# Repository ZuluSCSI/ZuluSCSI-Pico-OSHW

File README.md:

ZuluSCSI™ Pico Community Edition - Open Source Hardware
========================

This repository contains the KiCAD 7 schematic and PCB design files for the Pico-based ZuluSCSI™ SCSI to SD storage emulator, which is derived from the ZuluSCSI RP2040 board design. Firmware for ZuluSCSI is available at http://github.com/ZuluSCSI/ZuluSCSI-firmware.

This hardware design is licensed under the terms of the strongly reciprocal CERN OHL-S V2 license, which can be viewed in full at https://ohwr.org/cern_ohl_s_v2.txt and https://ohwr.org/cern_ohl_s_v2.pdf. 

ZuluSCSI™ is a registered trademark of Rabbit Hole Computing, and may not be used commercially without the express written consent of Rabbit Hole Computing. Individuals producing ZuluSCSI boards for personal use are hereby granted permission to use the ZuluSCSI trademark in a noncommercial capacity.

_Any_ use of the ZuluSCSI trademark in a **commercial** context requires prior written consent from Rabbit Hole Computing.

Generating fabrication files
----------------------------

The component part numbers are stored in KiCAD schematic.
Manufacturing files, including assembly BOM, can be generated using [KiKit](https://github.com/yaqwsx/KiKit).

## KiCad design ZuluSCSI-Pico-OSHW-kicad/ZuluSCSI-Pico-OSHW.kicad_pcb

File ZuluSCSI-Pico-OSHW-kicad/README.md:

ZuluSCSI™ Pico Community Edition - Open Source Hardware
========================

This repository contains the KiCAD 7 schematic and PCB design files for the Pico-based ZuluSCSI™ SCSI to SD storage emulator, which is derived from the ZuluSCSI RP2040 board design. Firmware for ZuluSCSI is available at http://github.com/ZuluSCSI/ZuluSCSI-firmware.

This hardware design is licensed under the terms of the strongly reciprocal CERN OHL-S V2 license, which can be viewed in full at https://ohwr.org/cern_ohl_s_v2.txt and https://ohwr.org/cern_ohl_s_v2.pdf. 

ZuluSCSI™ is a registered trademark of Rabbit Hole Computing, and may not be used commercially without the express written consent of Rabbit Hole Computing. Individuals producing ZuluSCSI boards for personal use are hereby granted permission to use the ZuluSCSI trademark in a noncommercial capacity.

_Any_ use of the ZuluSCSI trademark in a **commercial** context requires prior written consent from Rabbit Hole Computing.

Firmware for ZuluSCSI is licensed under the GNU GPL Version 3, and can be found at https://github.com/zuluscsi/ZuluSCSI-firmware

Generating fabrication files
----------------------------

The component part numbers are stored in KiCAD schematic.
Manufacturing files, including assembly BOM, can be generated using [KiKit](https://github.com/yaqwsx/KiKit).

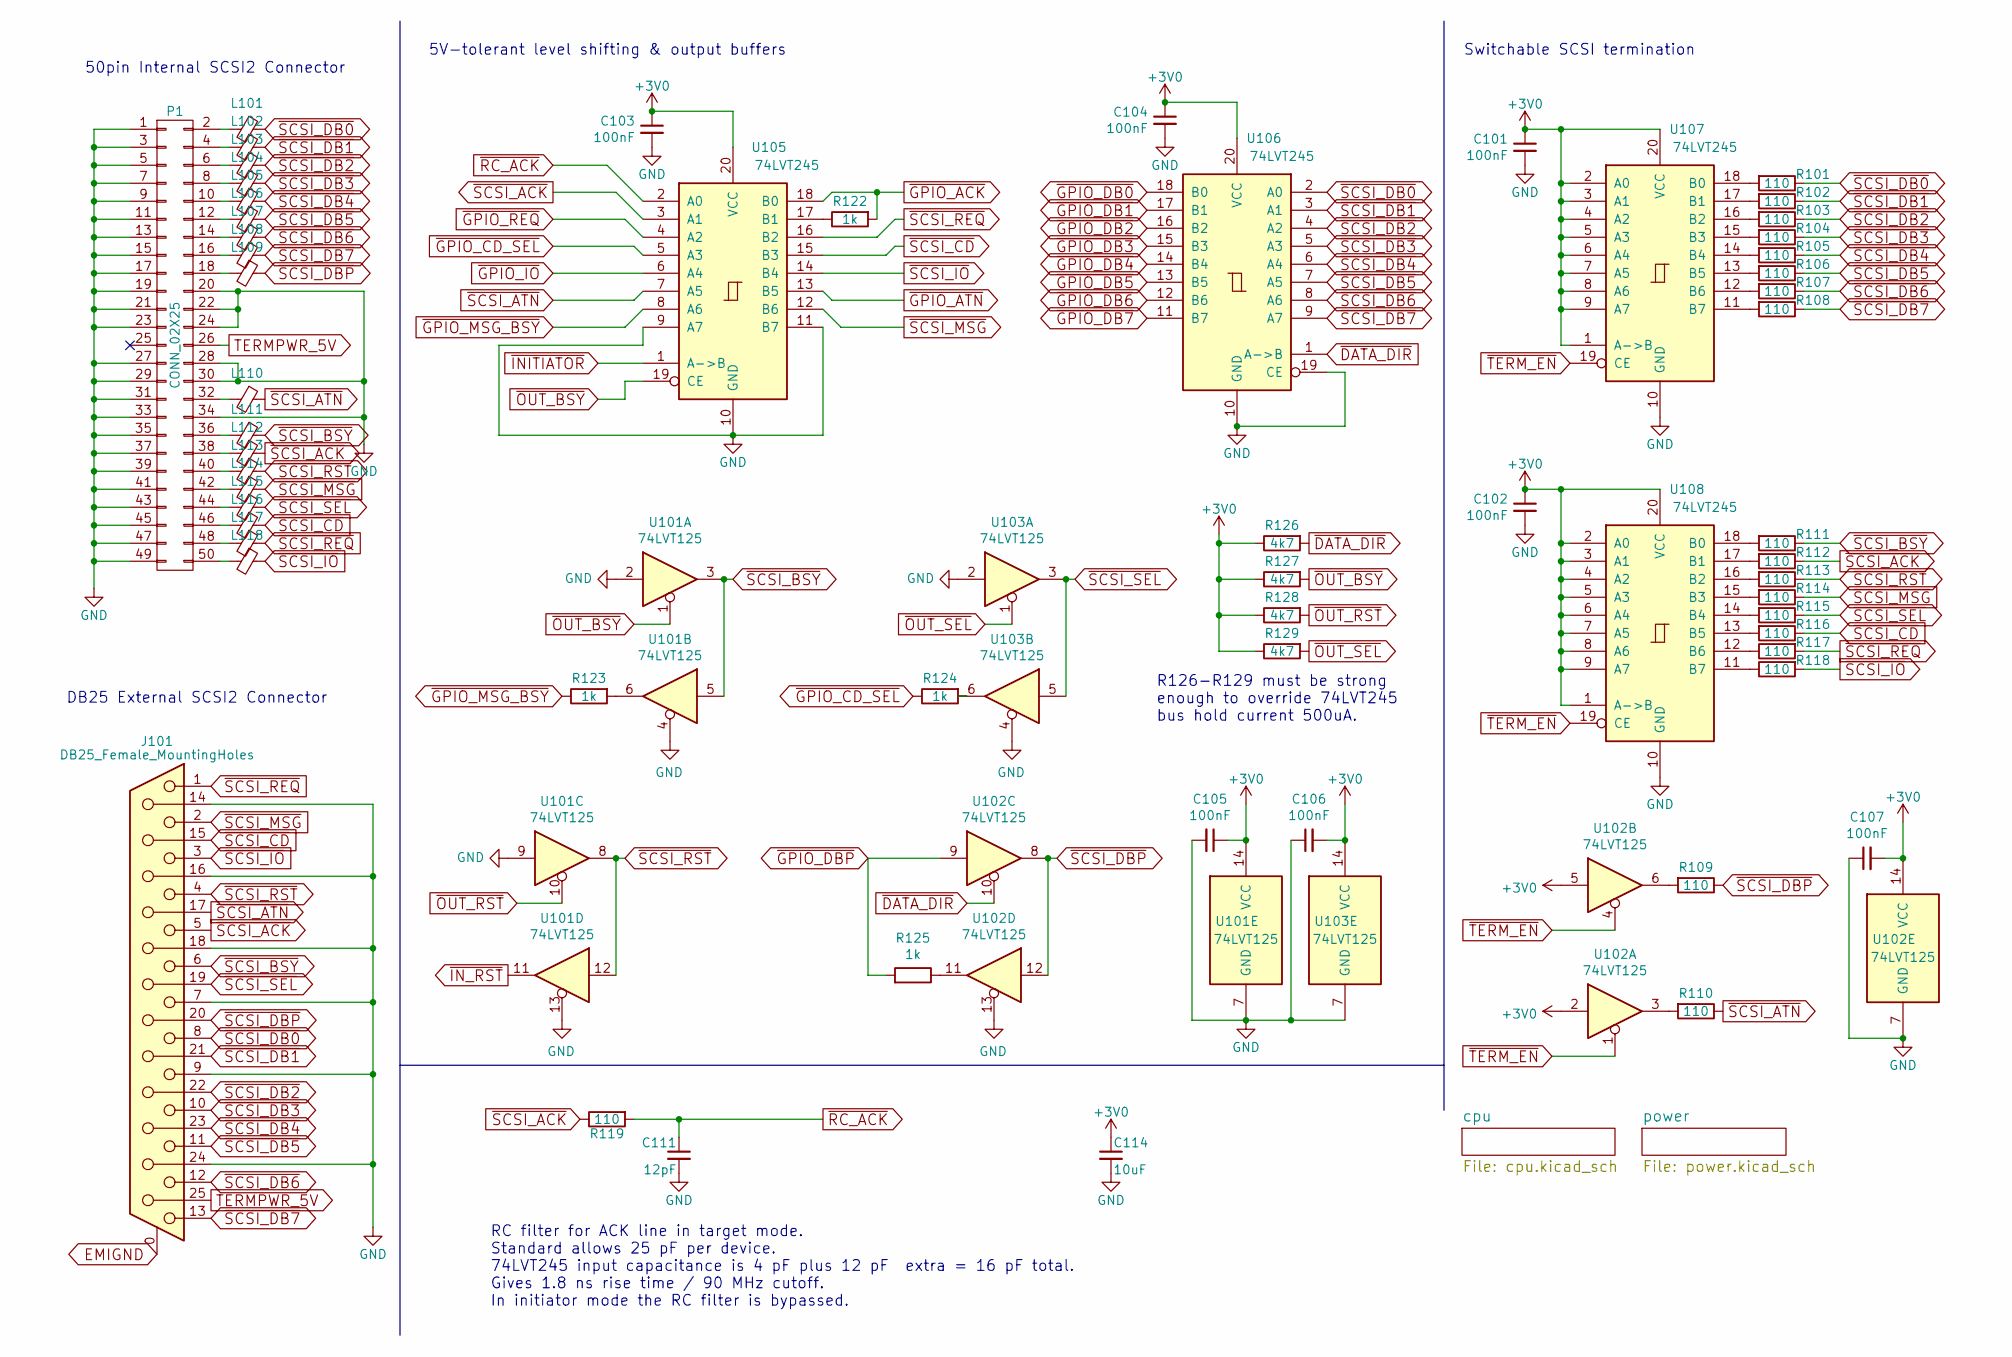
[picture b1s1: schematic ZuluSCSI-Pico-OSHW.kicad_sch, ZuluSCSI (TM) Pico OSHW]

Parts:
C101, C102, C103, C104, C105, C106, C107: 100nF; C_0603_1608Metric; PartNumber CL10B104KB8NNWC; LCSC C14663
C111: 12pF; C_0603_1608Metric; PartNumber C0603C120J5GAC7867; LCSC C38523
C114: 10uF; C_0805_2012Metric; PartNumber CL21A106KPFNNNG; LCSC C15850
J101: DB25_Female_MountingHoles; DSUB-25_Female_Horizontal_P2.77x2.84mm_EdgePinOffset9.90mm_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; LCSC N/A
L101, L102, L103, L104, L105, L106, L107, L108, L109, L110, L111, L112, L113, L114, L115, L116, L117, L118: Ferrite_Bead_Small; L_0603_1608Metric; PartNumber PE-0603FB601ST; LCSC C1002
P1: CONN_02X25; Pin_Header_Angled_2x25; LCSC N/A
R101, R102, R103, R104, R105, R106, R107, R108, R109, R110, R111, R112, R113, R114, R115, R116, R117, R118, R119: 110; R_0603_1608Metric; PartNumber RC0603FR-07110RL; LCSC C22781
R122, R123, R124, R125: 1k; R_0603_1608Metric; PartNumber RC0603JR-071KL; LCSC C21190
R126, R127, R128, R129: 4k7; R_0603_1608Metric; PartNumber RC0603JR-074K7L; LCSC C23162
U101, U102, U103: 74LVT125; SSOP_TSSOP-14_4.4x5mm_Pitch0.65mm_PCBWay-MaskClearance0.22mm; PartNumber 74LVTH125MTC; LCSC C7042
U105, U106, U107, U108: 74LVT245; SSOP_TSSOP-20_5.3x7.2mm_P0.65mm; PartNumber 74LVT245BBT20-13; LCSC C7057

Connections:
+3V0: C101.1, C102.1, C103.1, C104.1, C105.1, C106.2, C107.2, C114.1, R126.1, R127.1, R128.1, R129.1, U101.14 (VCC), U102.2, U102.5, U102.14 (VCC), U103.14 (VCC), U105.20 (VCC), U106.20 (VCC), U107.1 (A->B), U107.2 (A0), U107.3 (A1), U107.4 (A2), U107.5 (A3), U107.6 (A4), U107.7 (A5), U107.8 (A6), U107.9 (A7), U107.20 (VCC), U108.1 (A->B), U108.2 (A0), U108.3 (A1), U108.4 (A2), U108.5 (A3), U108.6 (A4), U108.7 (A5), U108.8 (A6), U108.9 (A7), U108.20 (VCC); also elsewhere on the board
EMIGND: J101.0 (PAD); also elsewhere on the board
GND: C101.2, C102.2, C103.2, C104.2, C105.2, C106.1, C107.1, C111.2, C114.2, J101.7, J101.9, J101.14, J101.16, J101.18, J101.24, P1.1, P1.3, P1.5, P1.7, P1.9, P1.11, P1.13, P1.15, P1.17, P1.19, P1.20, P1.21, P1.22, P1.23, P1.24, P1.27, P1.28, P1.29, P1.30, P1.31, P1.33, P1.34, P1.35, P1.37, P1.39, P1.41, P1.43, P1.45, P1.47, P1.49, U101.2, U101.4, U101.7 (GND), U101.9, U101.13, U102.7 (GND), U102.13, U103.2, U103.4, U103.7 (GND), U105.9 (A7), U105.10 (GND), U105.11 (B7), U106.10 (GND), U106.19 (CE), U107.10 (GND), U108.10 (GND); also elsewhere on the board
unnamed: L101.2, P1.2
unnamed: L102.2, P1.4
unnamed: L103.2, P1.6
unnamed: L104.2, P1.8
unnamed: L105.2, P1.10
unnamed: L106.2, P1.12
unnamed: L107.2, P1.14
unnamed: L108.2, P1.16
unnamed: L109.2, P1.18
unnamed: L110.2, P1.32
unnamed: L111.2, P1.36
unnamed: L112.2, P1.38
unnamed: L113.2, P1.40
unnamed: L114.2, P1.42
unnamed: L115.2, P1.44
unnamed: L116.2, P1.46
unnamed: L117.2, P1.48
unnamed: L118.2, P1.50
unnamed: R109.2, U102.6
unnamed: R110.2, U102.3
unnamed: R123.2, U101.6
unnamed: R124.2, U103.6
unnamed: R125.1, U102.11
unnamed: R122.1, U105.17 (B1)
unnamed: R101.2, U107.18 (B0)
unnamed: R102.2, U107.17 (B1)
unnamed: R103.2, U107.16 (B2)
unnamed: R104.2, U107.15 (B3)
unnamed: R105.2, U107.14 (B4)
unnamed: R106.2, U107.13 (B5)
unnamed: R107.2, U107.12 (B6)
unnamed: R108.2, U107.11 (B7)
unnamed: R111.2, U108.18 (B0)
unnamed: R112.2, U108.17 (B1)
unnamed: R113.2, U108.16 (B2)
unnamed: R114.2, U108.15 (B3)
unnamed: R115.2, U108.14 (B4)
unnamed: R116.2, U108.13 (B5)
unnamed: R117.1, U108.12 (B6)
unnamed: R118.1, U108.11 (B7)
TERMPWR_5V: J101.25, P1.26; also elsewhere on the board
~DATA_DIR: R126.2, U102.10, U106.1 (A->B); also elsewhere on the board
~GPIO_ACK: R122.2, U105.18 (B0); also elsewhere on the board
~GPIO_ATN: U105.13 (B5); also elsewhere on the board
~GPIO_CD_SEL: R124.1, U105.5 (A3); also elsewhere on the board
~GPIO_DB0: U106.18 (B0); also elsewhere on the board
~GPIO_DB1: U106.17 (B1); also elsewhere on the board
~GPIO_DB2: U106.16 (B2); also elsewhere on the board
~GPIO_DB3: U106.15 (B3); also elsewhere on the board
~GPIO_DB4: U106.14 (B4); also elsewhere on the board
~GPIO_DB5: U106.13 (B5); also elsewhere on the board
~GPIO_DB6: U106.12 (B6); also elsewhere on the board
~GPIO_DB7: U106.11 (B7); also elsewhere on the board
~GPIO_DBP: R125.2, U102.9; also elsewhere on the board
~GPIO_IO: U105.6 (A4); also elsewhere on the board
~GPIO_MSG_BSY: R123.1, U105.8 (A6); also elsewhere on the board
~GPIO_REQ: U105.4 (A2); also elsewhere on the board
~INITIATOR: U105.1 (A->B); also elsewhere on the board
~IN_RST: U101.11; also elsewhere on the board
~OUT_BSY: R127.2, U101.1, U105.19 (CE); also elsewhere on the board
~OUT_RST: R128.2, U101.10; also elsewhere on the board
~OUT_SEL: R129.2, U103.1; also elsewhere on the board
~RC_ACK: C111.1, R119.2, U105.2 (A0)
~SCSI_ACK: J101.5, L112.1, R112.1, R119.1, U105.3 (A1)
~SCSI_ATN: J101.17, L110.1, R110.1, U105.7 (A5)
~SCSI_BSY: J101.6, L111.1, R111.1, U101.3, U101.5
~SCSI_CD: J101.15, L116.1, R116.1, U105.15 (B3)
~SCSI_DB0: J101.8, L101.1, R101.1, U106.2 (A0)
~SCSI_DB1: J101.21, L102.1, R102.1, U106.3 (A1)
~SCSI_DB2: J101.22, L103.1, R103.1, U106.4 (A2)
~SCSI_DB3: J101.10, L104.1, R104.1, U106.5 (A3)
~SCSI_DB4: J101.23, L105.1, R105.1, U106.6 (A4)
~SCSI_DB5: J101.11, L106.1, R106.1, U106.7 (A5)
~SCSI_DB6: J101.12, L107.1, R107.1, U106.8 (A6)
~SCSI_DB7: J101.13, L108.1, R108.1, U106.9 (A7)
~SCSI_DBP: J101.20, L109.1, R109.1, U102.8, U102.12
~SCSI_IO: J101.3, L118.1, R118.2, U105.14 (B4)
~SCSI_MSG: J101.2, L114.1, R114.1, U105.12 (B6)
~SCSI_REQ: J101.1, L117.1, R117.2, U105.16 (B2)
~SCSI_RST: J101.4, L113.1, R113.1, U101.8, U101.12
~SCSI_SEL: J101.19, L115.1, R115.1, U103.3, U103.5
~TERM_EN: U102.1, U102.4, U107.19 (CE), U108.19 (CE); also elsewhere on the board

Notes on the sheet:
Switchable SCSI termination
R126-R129 must be strong enough to override 74LVT245 bus hold current 500uA.
5V-tolerant level shifting & output buffers
50pin Internal SCSI2 Connector
DB25 External SCSI2 Connector
RC filter for ACK line in target mode. Standard allows 25 pF per device. 74LVT245 input capacitance is 4 pF plus 12 pF extra = 16 pF total. Gives 1.8 ns rise time / 90 MHz cutoff. In initiator mode the RC filter is bypassed.

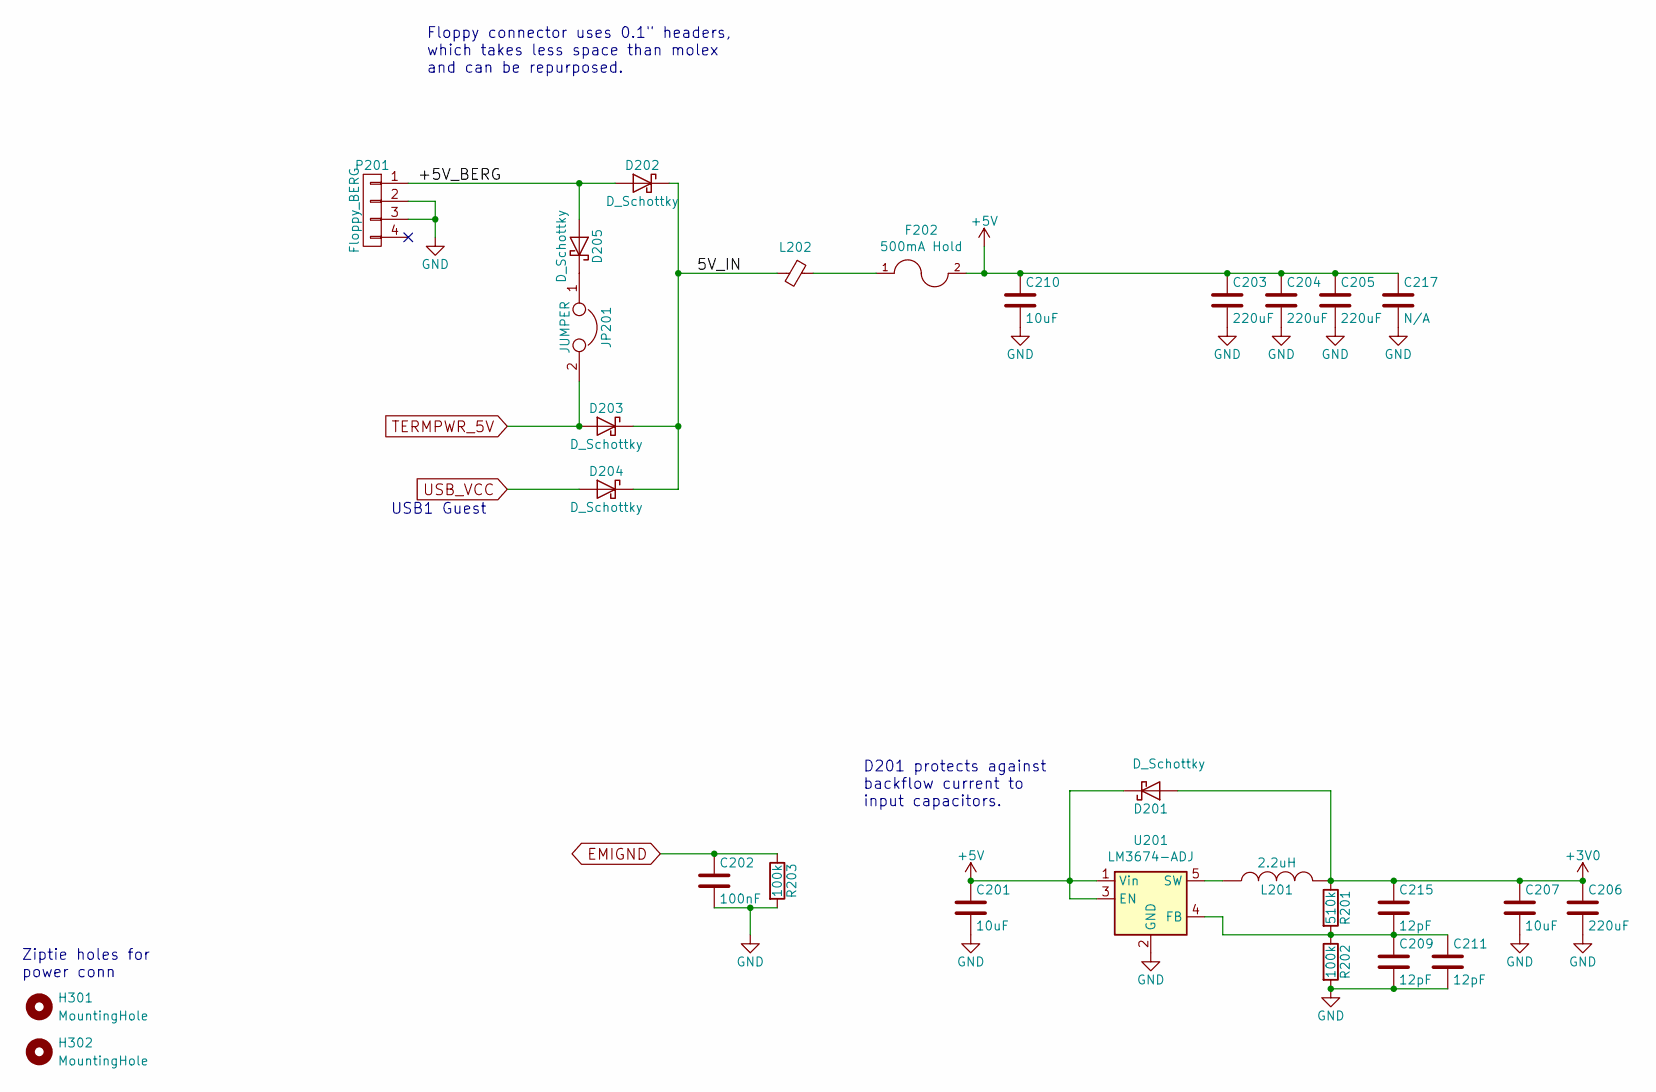
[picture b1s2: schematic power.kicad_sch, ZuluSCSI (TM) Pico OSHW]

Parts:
C201, C207, C210: 10uF; C_0805_2012Metric; PartNumber CL21A106KPFNNNG; LCSC C15850
C202: 100nF; C_0603_1608Metric; PartNumber CL10B104KB8NNWC; LCSC C14663
C203, C204, C205, C206: 220uF; CP_Elec_6.3x7.7; PartNumber UUD1C221MCL1GS; LCSC C2887273
C209, C211, C215: 12pF; C_0603_1608Metric; PartNumber C0603C120J5GAC7867; LCSC C38523
C217: N/A; CP_Radial_D10.0mm_P5.00mm; LCSC N/A
D201, D202, D203, D204, D205: D_Schottky; D_SOD-123; PartNumber MBRX120LF-TP; LCSC C8598
F202: 500mA Hold; Fuse_1206_3216Metric; PartNumber 0ZCJ0050FF2G; LCSC C369160
H301, H302: MountingHole; MountingHole_2.7mm_M2.5; LCSC N/A
JP201: JUMPER; PinHeader_1x02_P2.54mm_Vertical; LCSC N/A
L201: 2.2uH; Inductor_1008; PartNumber DFE252012P-2R2M=P2; LCSC C86092
L202: Ferrite_Bead_Small; L_0603_1608Metric; PartNumber PE-0603FB601ST; LCSC C1002
P201: Floppy_BERG; floppy-berg; LCSC N/A
R201: 510k; R_0603_1608Metric; PartNumber RC0603FR-07510KL; LCSC C23192
R202, R203: 100k; R_0603_1608Metric; PartNumber RC0603FR-07100KL; LCSC C25803
U201: LM3674-ADJ; TSOT-23-5; PartNumber LM3674MFX-ADJ/NOPB; LCSC C52027

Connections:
+3V0: C206.1, C207.1, C215.1, D201.2 (A), L201.2, R201.1; also elsewhere on the board
+5V: C201.1, C203.1, C204.1, C205.1, C210.1, C217.1, D201.1 (K), F202.2, U201.1 (Vin), U201.3 (EN); also elsewhere on the board
/power/5V_IN: D202.1 (K), D203.1 (K), D204.1 (K), L202.2
/power/+5V_BERG: D202.2 (A), D205.2 (A), P201.1
EMIGND: C202.1, R203.1; also elsewhere on the board
GND: C201.2, C202.2, C203.2, C204.2, C205.2, C206.2, C207.2, C209.2, C210.2, C211.2, C217.2, P201.2, P201.3, R202.2, R203.2, U201.2 (GND); also elsewhere on the board
unnamed: D205.1 (K), JP201.1
unnamed: F202.1, L202.1
unnamed: C209.1, C211.1, C215.2, R201.2, R202.1, U201.4 (FB)
unnamed: L201.1, U201.5 (SW)
TERMPWR_5V: D203.2 (A), JP201.2; also elsewhere on the board
USB_VCC: D204.2 (A); also elsewhere on the board

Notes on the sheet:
Floppy connector uses 0.1" headers, which takes less space than molex and can be repurposed.
USB1 Guest
D201 protects against backflow current to input capacitors.
Ziptie holes for power conn

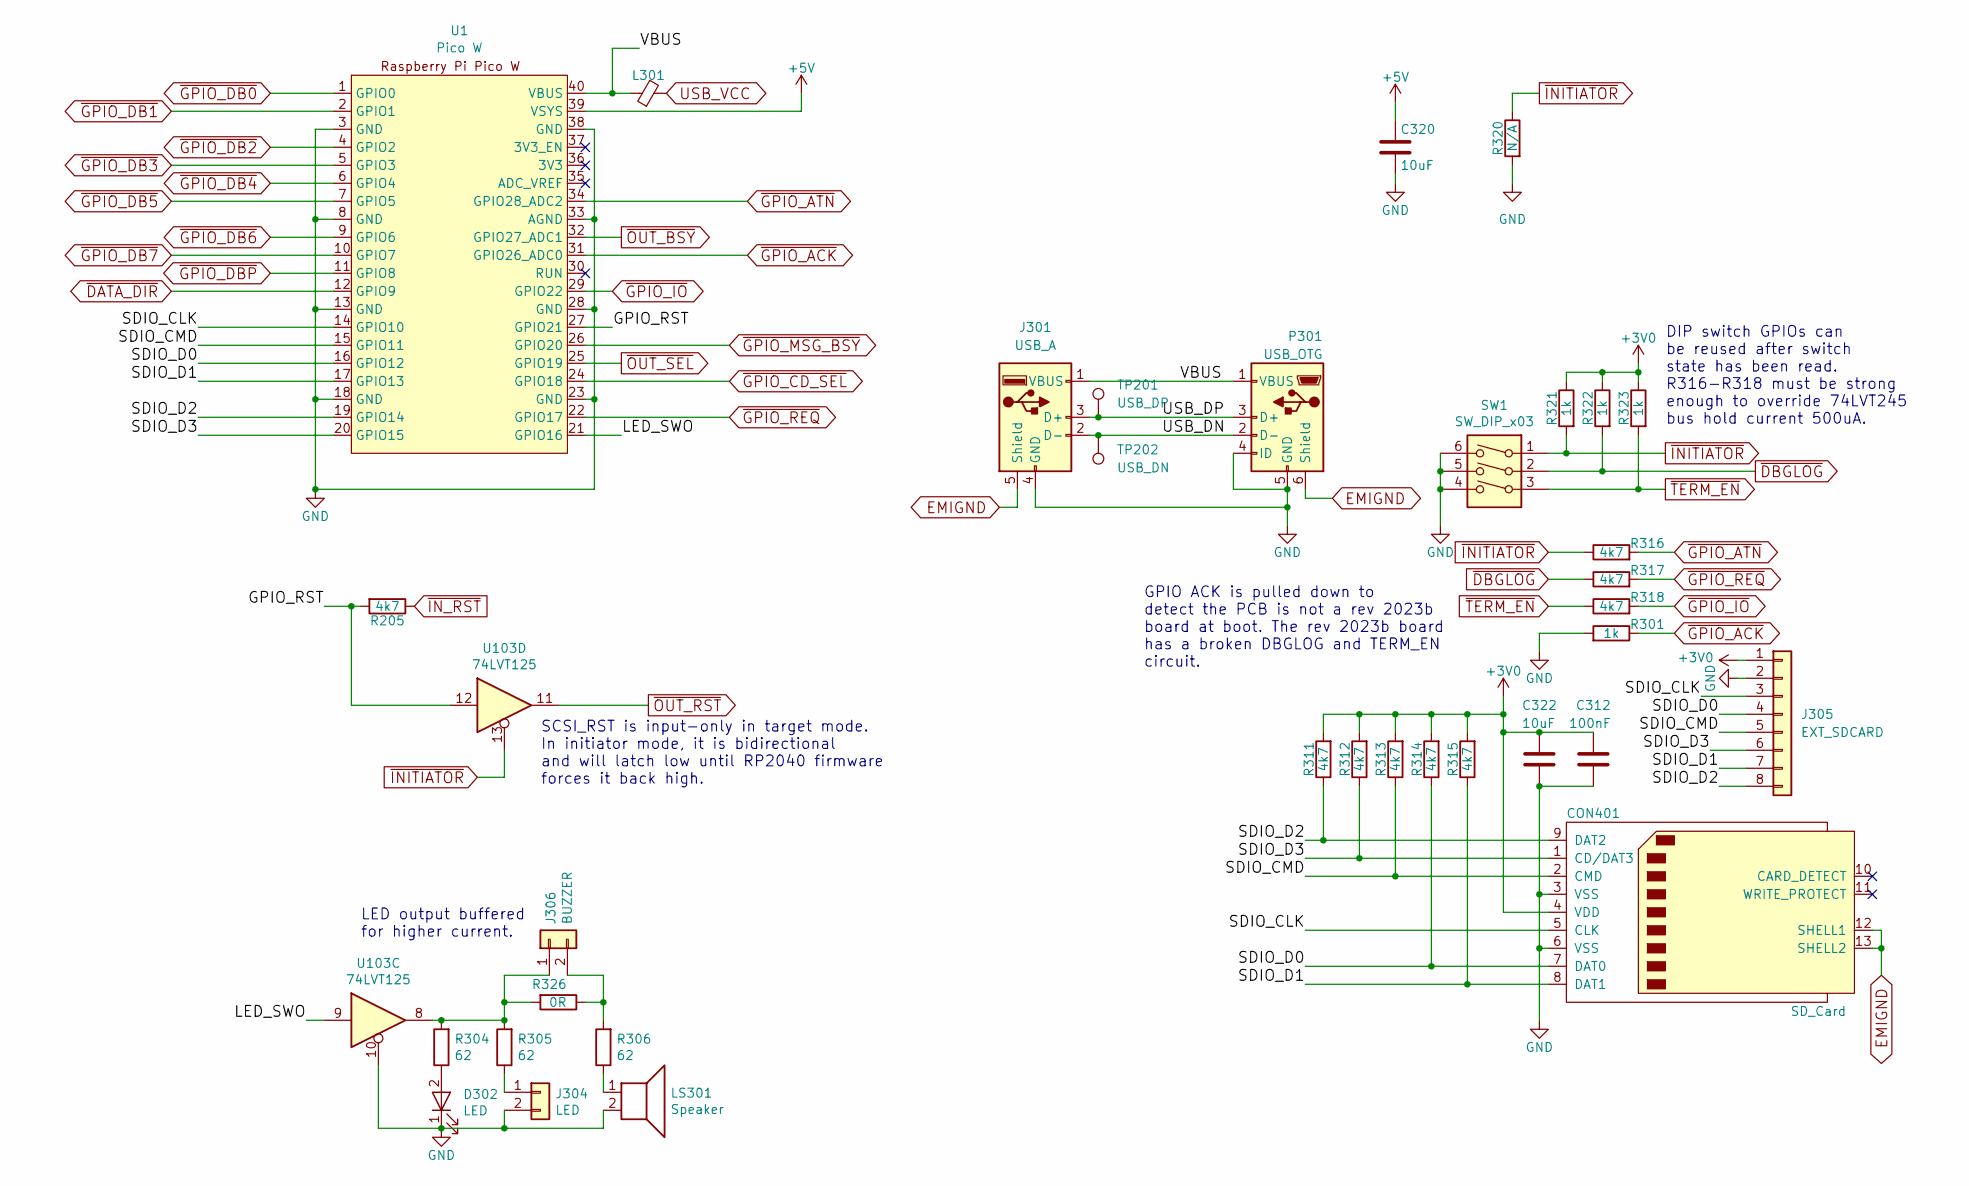
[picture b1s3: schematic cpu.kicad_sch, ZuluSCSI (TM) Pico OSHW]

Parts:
C312: 100nF; C_0603_1608Metric; PartNumber CL10B104KB8NNWC; LCSC C14663
C320, C322: 10uF; C_0805_2012Metric; PartNumber CL21A106KPFNNNG; LCSC C15850
CON401: SD_Card; SD-FCI-10067847-001; PartNumber 10067847-001RLF; LCSC C410353
D302: LED; LED_0805_2012Metric; PartNumber LY R976-PS-36; LCSC C434435
J301: USB_A; USB_A_Molex_105057_Vertical; LCSC N/A
J304: LED; PinHeader_1x02_P2.54mm_Vertical; LCSC N/A
J305: EXT_SDCARD; PinHeader_1x08_P2.54mm_Vertical; JLCPCB_IGNORE do not fit
J306: BUZZER; PinHeader_1x02_P2.54mm_Vertical; LCSC N/A
L301: Ferrite_Bead_Small; L_0603_1608Metric; PartNumber PE-0603FB601ST; LCSC C1002
LS301: Speaker; Buzzer_TDK_PS1240P02BT_D12.2mm_H6.5mm; LCSC N/A
P301: USB_OTG; USB_Micro-B_Amphenol_10118194_Horizontal; PartNumber 10118194-0001LF; LCSC C132563
R205, R311, R312, R313, R314, R315, R316, R317, R318: 4k7; R_0603_1608Metric; PartNumber RC0603JR-074K7L; LCSC C23162
R301, R321, R322, R323: 1k; R_0603_1608Metric; PartNumber RC0603JR-071KL; LCSC C21190
R304, R305, R306: 62; R_0603_1608Metric; PartNumber RC0603FR-0762RL; LCSC C25252
R320: N/A; R_0402_1005Metric; LCSC N/A
R326: 0R; R_0603_1608Metric; LCSC N/A
SW1: SW_DIP_x03; SW_DIP_SPSTx03_Slide_6.7x9.18mm_W8.61mm_P2.54mm_LowProfile; PartNumber 219-3MSTR; LCSC C319040
TP201: USB_DP; TestPoint_Pad_2.0x2.0mm; LCSC N/A
TP202: USB_DN; TestPoint_Pad_2.0x2.0mm; LCSC N/A
U1: Pico W; RPi_Pico_W_SMD_TH; LCSC N/A
U103: 74LVT125; SSOP_TSSOP-14_4.4x5mm_Pitch0.65mm_PCBWay-MaskClearance0.22mm; PartNumber 74LVTH125MTC; LCSC C7042

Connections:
+3V0: C312.2, C322.2, CON401.4 (VDD), J305.1, R311.2, R312.2, R313.2, R314.2, R315.2, R321.1, R322.1, R323.1; also elsewhere on the board
+5V: C320.1, U1.39 (VSYS); also elsewhere on the board
/cpu/GPIO_RST: R205.2, U1.27 (GPIO21), U103.12
/cpu/LED_SWO: U1.21 (GPIO16), U103.9
/cpu/SDIO_CLK: CON401.5 (CLK), J305.3, U1.14 (GPIO10)
/cpu/SDIO_CMD: CON401.2 (CMD), J305.5, R313.1, U1.15 (GPIO11)
/cpu/SDIO_D0: CON401.7 (DAT0), J305.4, R314.1, U1.16 (GPIO12)
/cpu/SDIO_D1: CON401.8 (DAT1), J305.7, R315.1, U1.17 (GPIO13)
/cpu/SDIO_D2: CON401.9 (DAT2), J305.8, R311.1, U1.19 (GPIO14)
/cpu/SDIO_D3: CON401.1 (CD/DAT3), J305.6, R312.1, U1.20 (GPIO15)
/cpu/USB_DN: J301.2 (D-), P301.2 (D-), TP202.1
/cpu/USB_DP: J301.3 (D+), P301.3 (D+), TP201.1
/cpu/VBUS: J301.1 (VBUS), L301.1, P301.1 (VBUS), U1.40 (VBUS)
EMIGND: CON401.12 (SHELL1), CON401.13 (SHELL2), J301.5 (Shield), P301.6 (Shield); also elsewhere on the board
GND: C312.1, C320.2, C322.1, CON401.3 (VSS), CON401.6 (VSS), D302.1 (K), J301.4 (GND), J304.2, J305.2, LS301.2, P301.4 (ID), P301.5 (GND), R301.2, R320.2, SW1.4, SW1.5, SW1.6, U1.3 (GND), U1.8 (GND), U1.13 (GND), U1.18 (GND), U1.23 (GND), U1.28 (GND), U1.33 (AGND), U1.38 (GND), U103.10; also elsewhere on the board
unnamed: D302.2 (A), R304.1
unnamed: J304.1, R305.1
unnamed: J306.1, R304.2, R305.2, R326.2, U103.8
unnamed: J306.2, R306.2, R326.1
unnamed: LS301.1, R306.1
USB_VCC: L301.2; also elsewhere on the board
~DATA_DIR: U1.12 (GPIO9); also elsewhere on the board
~DBGLOG: R317.1, R322.2, SW1.2
~GPIO_ACK: R301.1, U1.31 (GPIO26_ADC0); also elsewhere on the board
~GPIO_ATN: R316.2, U1.34 (GPIO28_ADC2); also elsewhere on the board
~GPIO_CD_SEL: U1.24 (GPIO18); also elsewhere on the board
~GPIO_DB0: U1.1 (GPIO0); also elsewhere on the board
~GPIO_DB1: U1.2 (GPIO1); also elsewhere on the board
~GPIO_DB2: U1.4 (GPIO2); also elsewhere on the board
~GPIO_DB3: U1.5 (GPIO3); also elsewhere on the board
~GPIO_DB4: U1.6 (GPIO4); also elsewhere on the board
~GPIO_DB5: U1.7 (GPIO5); also elsewhere on the board
~GPIO_DB6: U1.9 (GPIO6); also elsewhere on the board
~GPIO_DB7: U1.10 (GPIO7); also elsewhere on the board
~GPIO_DBP: U1.11 (GPIO8); also elsewhere on the board
~GPIO_IO: R318.2, U1.29 (GPIO22); also elsewhere on the board
~GPIO_MSG_BSY: U1.26 (GPIO20); also elsewhere on the board
~GPIO_REQ: R317.2, U1.22 (GPIO17); also elsewhere on the board
~INITIATOR: R316.1, R320.1, R321.2, SW1.1, U103.13; also elsewhere on the board
~IN_RST: R205.1; also elsewhere on the board
~OUT_BSY: U1.32 (GPIO27_ADC1); also elsewhere on the board
~OUT_RST: U103.11; also elsewhere on the board
~OUT_SEL: U1.25 (GPIO19); also elsewhere on the board
~TERM_EN: R318.1, R323.2, SW1.3; also elsewhere on the board

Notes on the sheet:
GPIO ACK is pulled down to detect the PCB is not a rev 2023b board at boot. The rev 2023b board has a broken DBGLOG and TERM_EN circuit.
DIP switch GPIOs can be reused after switch state has been read. R316-R318 must be strong enough to override 74LVT245 bus hold current 500uA.
SCSI_RST is input-only in target mode. In initiator mode, it is bidirectional and will latch low until RP2040 firmware forces it back high.
LED output buffered for higher current.

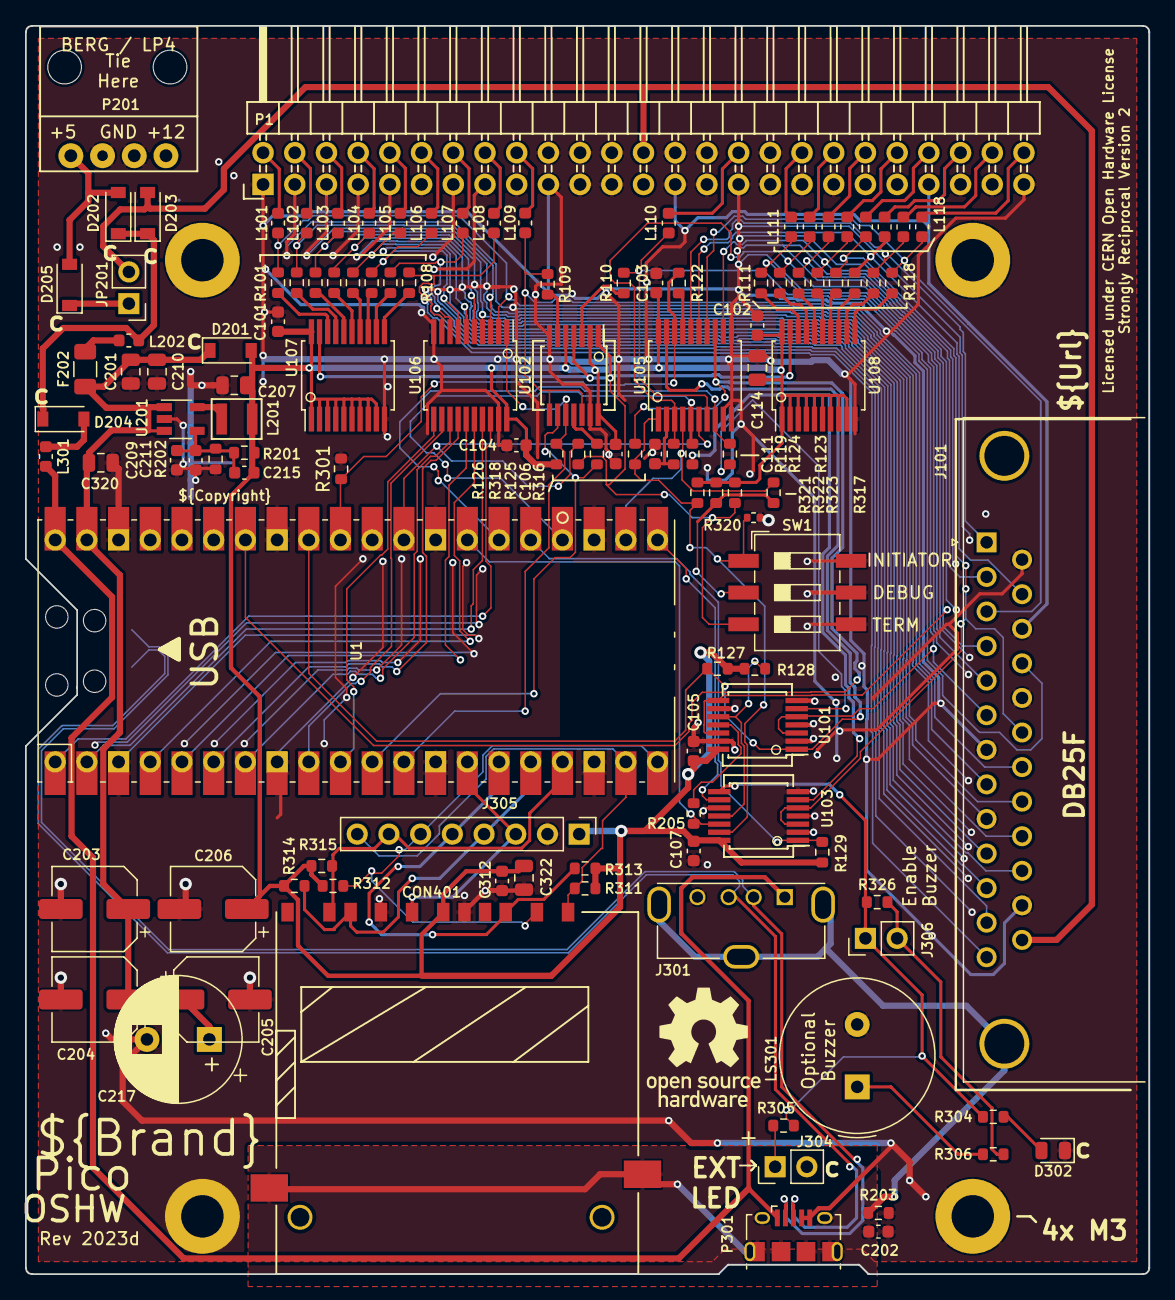
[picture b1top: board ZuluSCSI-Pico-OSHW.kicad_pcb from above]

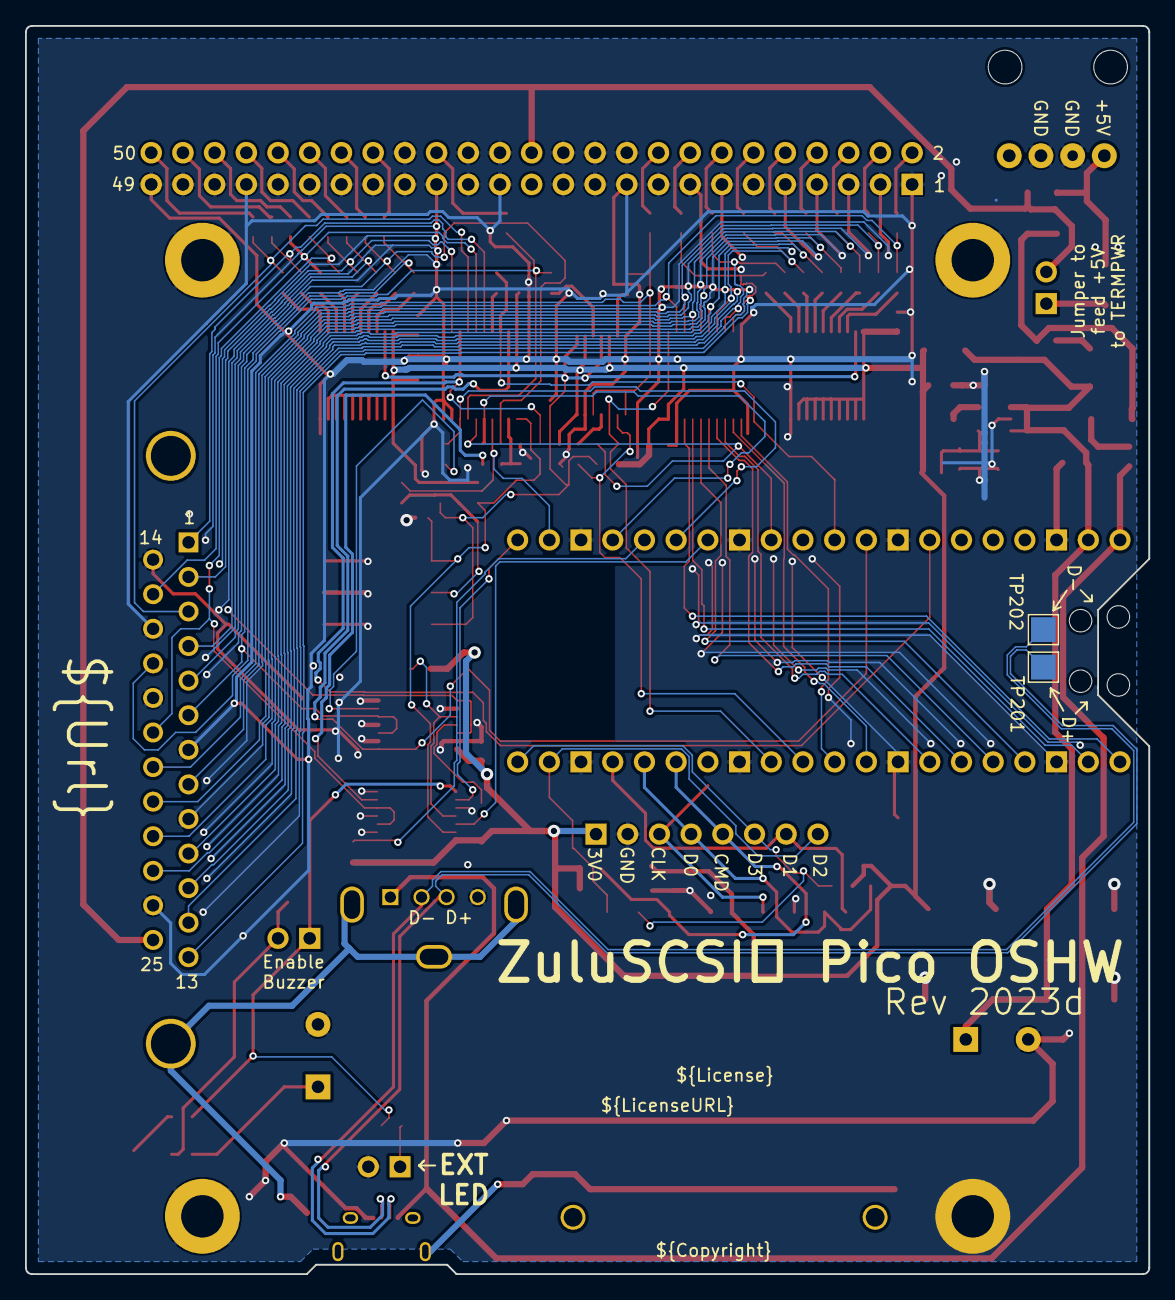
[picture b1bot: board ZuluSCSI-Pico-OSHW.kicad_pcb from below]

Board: 2 copper layers, 90.0 x 100.0 mm, 125 parts (2 on the bottom side), 110 nets.

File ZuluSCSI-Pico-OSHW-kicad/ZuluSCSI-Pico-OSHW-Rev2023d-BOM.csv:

Designator,Footprint,Manufacturer P/N,Quantity,Value,LCSC P/N,Digi-Key P/N,Mouser P/N
"C101, C102, C103, C104, C105, C106, C107, C202, C312",603,CC0603KRX7R9BB104,9,100nF,C14663,311-1344-1-ND,603-CC603KRX7R9BB104
"C111, C209, C211, C215",603,CL10C120JB8NNNC,4,12pF,C38523,445-14057-1-ND,187-CL10C120JB8NNNC
"C114, C201, C207, C210, C320, C322",805,CL21A106KAYNNNE,6,10uF,C15850,1276-2891-1-ND,187-CL21A106KAYNNNE
"C203, C204, C205, C206",CP_Elec_6.3x7.7,RVT220UF16V67RV0015,4,220uF,C2887273,732-8422-1-ND,710-865080345012
C217,Radial through-hole D10.0mm by P5.00mm,UVY1C102MPD1TD,1,1000uF,N/A,493-14736-1-ND,647-UVY1C102MPD1TD
CON401,FCI 10067847-001 or SD-111,SD-111,1,SD Card Socket,C410353,609-3956-2-ND,649-10067847-001RLF
"D201, D202, D203, D204, D205",SOD-123,B5819W SL,5,D_Schottky,C8598,SM5819PL-TPMSCT-ND,833-SM5819PL-TP
D302,805,SZYY0805YG,1,LED,C434435,350-2044-1-ND ,645-598-8170-107F
F202,1206,JK-nSMD050-24,1,500mA Hold PTC,C369160,507-1802-1-ND,530-0ZCJ0050FF2G
J101,Optional DSUB-25 Female,D25S33E4PA00LF,1,N/A,N/A,609-5879-ND,649-D25S33E4PA00LF
J301,Optional USB-A,Molex 105057,1,N/A,N/A,WM8672-ND,538-105057-0001
J304,2-pin 2.54mm Pin Header,Generic,1,Optional External LED header,N/A,952-2262-ND,855-M20-9990246
JP201,2-pin 2.54mm Pin Header,Generic,0,Optional Back Feed Jumper,N/A,952-2262-ND,855-M20-9990246
"L101, L102, L103, L104, L105, L106, L107, L108, L109, L110, L111, L112, L113, L114, L115, L116, L117, L118, L202, L301",603,GZ1608D601TF,20,450mΩ ±25% 600Ω@100MHz,C1002,3442-GZ1608D601TFCT-ND,815-ACML-0603H-601
L201,1008,LQM2HPN2R2MG0L,1,2.2uH,C86092,490-5114-1-ND,81-LQM2HPN2R2MG0L
LS301,Optional Piezo Buzzer,TDK PS1240P02BT,1,N/A,C76871,445-2525-1-ND ,810-PS1240P02BT
P1,50-pin right angle IDC (SCSI),Z-231012050106,1,2X25 right angle box header,C221060,3M157291-ND,30350-5002HB
P201,Optional Floppy power connector,171826-4,1,Floppy-style BERG/LP4,C590635,A112643-ND,571-1718264
P301,Optional USB Micro-B,10118194-0001LF,1,Micro USB OTG (optional),C132563,609-4618-1-ND,649-10118194-0001LF
"R101, R102, R103, R104, R105, R106, R107, R108, R109, R110, R111, R112, R113, R114, R115, R116, R117, R118, R119",603,0603WAF1100T5E,19,110,C22781,311-4.70KHRCT-ND,603-RC0603FR-074K7L
"R122, R123, R124, R125, R301, R321, R322, R323",603,0603WAF1001T5E,8,1k,C21190,13-AC0603FR-131KLCT-ND ,603-AC0603FR-131KL
"R126, R127, R128, R129, R205, R311, R312, R313, R314, R315, R316, R317, R318",603,0603WAF4701T5E,13,4k7,C23162,311-4.70KHRCT-ND,603-RC0603FR-074K7L
R201,603,0603WAF5103T5E,1,510k,C23192,311-510KHRCT-ND,603-RC0603FR-07510KL
"R202, R203",603,0603WAF1003T5E,2,100k,C25803,311-100KHRCT-ND ,603-RC0603FR-07100KL
"R304, R305, R306",603,0603WAJ0620T5E,3,62,C25252,311-62.0HRCT-ND,603-RC0603FR-0762RL
R320,402,N/A,0,None (DNP),N/A,N/A,N/A
SW1,"DIP slide switch, SPSTx03",DSIC03LS-P,1,SW_DIP_x03,C319040,CT2043ST-ND,774-2043ST
U1,"Raspberry Pi Pico (Pico, Pico H, or Pico W)",Pico,1,,N/A,N/A,N/A
"U101, U102, U103",SSOP or TSSOP,SN74LVTH125PWR,3,74LVT125,C7042,296-8660-1-ND,595-SN74LVTH125PWR
"U105, U106, U107, U108",SSOP or TSSOP,SN74LVTH245APWR,4,74LVT245,C7057,296-48966-1-ND,595-SN74LVTH245APWR
U201,TSOT-23-5,LM3674MFX-ADJ/NOPB,1,LM3674-ADJ,C882787,296-43049-1-ND,926-LM3674MFXADJNOPB

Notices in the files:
ZuluSCSI-Pico-OSHW-kicad/ZuluSCSI-Pico-OSHW.kicad_pcb:
Licensed under CERN Open Hardware License
parts and their libraries:
Copyright: ©2023 Rabbit Hole Computing LLC
License: Licensed under CERN Open Hardware License Strongly Reciprocal Version 2
LicenseURL: https://spdx.org/licenses/CERN-OHL-S-2.0.html
